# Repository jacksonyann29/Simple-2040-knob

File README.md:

# Simple-2040-knob
 PCB Design for a single rotary encoder HID, based on a RP2040 microcontroller.

## About
The goal of this project was to get more practice designing PCBs by implementing a microcontroller directly on a PCB. The current iteration successfully works except for USB programming and communication. USB power works, and programming over the SWD pins also works demonstrating that the RP2040 and flash were correctly configured including the crystal oscillator (at least for the simple led blink code tested on the device).

## Future Changes
*	Shorten the USB traces, use a surface mount usb port and double check impedance so USB communication will work.
*	Replace the crystal circuit with an external crystal oscillator IC which would hopefully be simpler to implement and more robust.
*	Add hardware debouncing to the encoder implementation.

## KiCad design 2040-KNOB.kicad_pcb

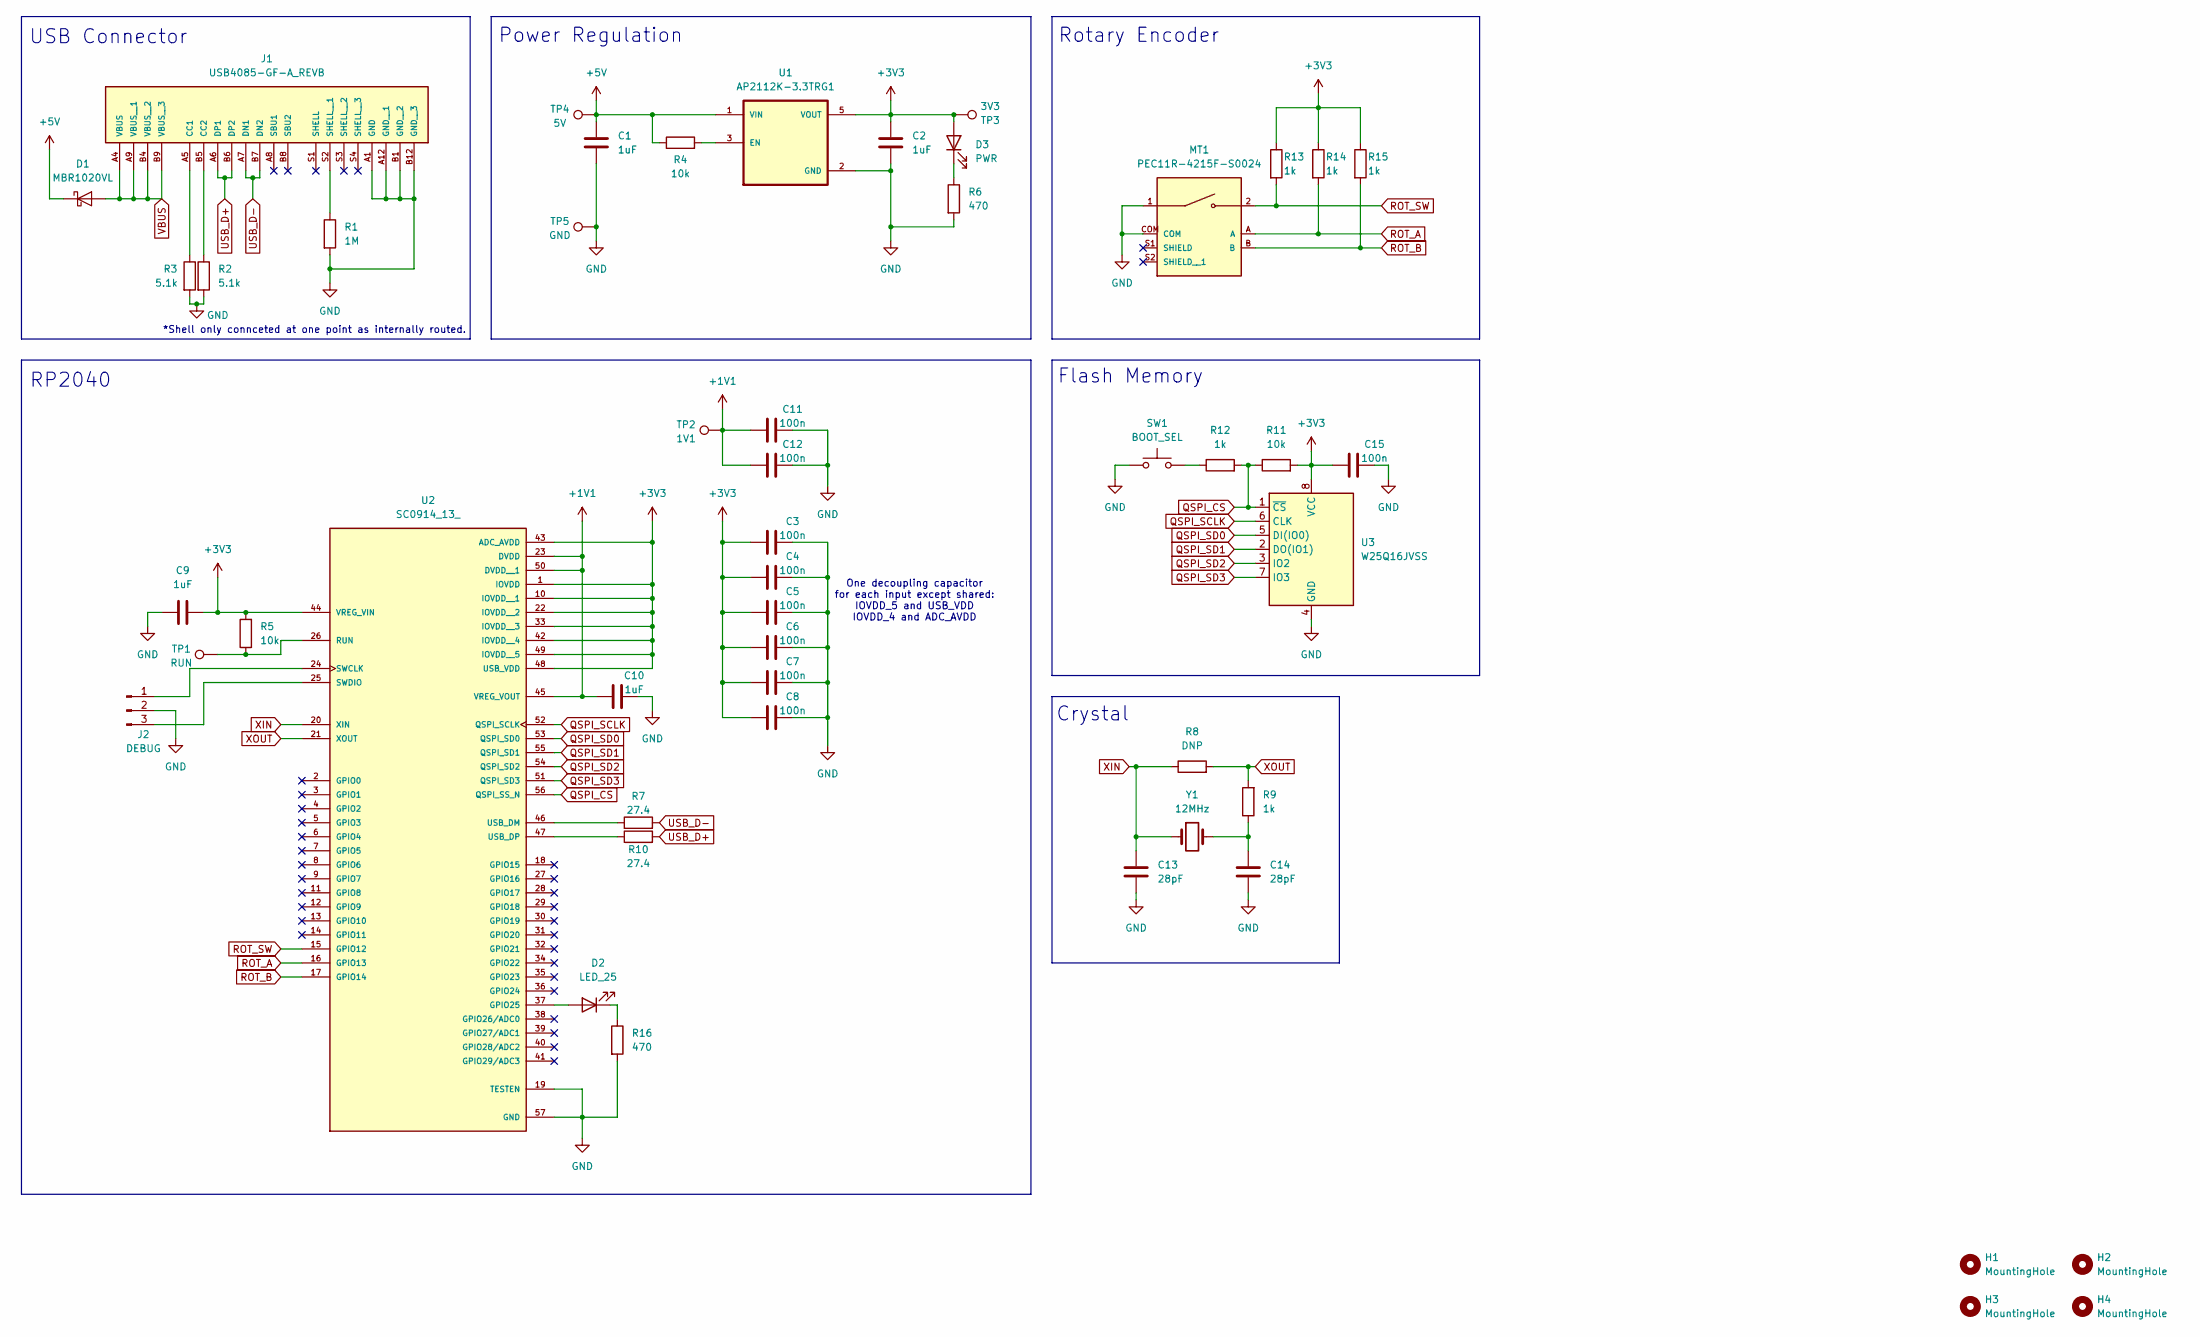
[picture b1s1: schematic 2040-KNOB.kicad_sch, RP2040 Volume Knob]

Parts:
C1, C2: 1uF; C_1206_3216Metric_Pad1.33x1.80mm_HandSolder
C3, C4, C5, C6, C7, C8, C11, C12, C15: 100n; C_0603_1608Metric_Pad1.08x0.95mm_HandSolder
C9, C10: 1uF; C_0805_2012Metric_Pad1.18x1.45mm_HandSolder
C13, C14: 28pF; C_0805_2012Metric_Pad1.18x1.45mm_HandSolder
D1: MBR1020VL; D_SOD-123F
D2: LED_25; LED_1206_3216Metric_Pad1.42x1.75mm_HandSolder
D3: PWR; LED_1206_3216Metric_Pad1.42x1.75mm_HandSolder
H1, H2, H3, H4: MountingHole; MountingHole_3.2mm_M3_ISO7380_Pad
J1: USB4085-GF-A_REVB; GCT_USB4085-GF-A_REVB; PARTREV B
J2: DEBUG; PinHeader_1x03_P2.54mm_Vertical
MT1: PEC11R-4215F-S0024; XDCR_PEC11R-4215F-S0024; PARTREV Rev. 09/19
R1: 1M; R_1206_3216Metric_Pad1.30x1.75mm_HandSolder
R2, R3: 5.1k; R_1206_3216Metric_Pad1.30x1.75mm_HandSolder
R4, R5, R11: 10k; R_1206_3216Metric_Pad1.30x1.75mm_HandSolder
R6, R16: 470; R_1206_3216Metric_Pad1.30x1.75mm_HandSolder
R7, R10: 27.4; R_0603_1608Metric_Pad0.98x0.95mm_HandSolder
R8: DNP; R_0603_1608Metric_Pad0.98x0.95mm_HandSolder
R9: 1k; R_0603_1608Metric_Pad0.98x0.95mm_HandSolder
R12, R13, R14, R15: 1k; R_1206_3216Metric_Pad1.30x1.75mm_HandSolder
SW1: BOOT_SEL; SW_PUSH_6mm
TP1: RUN; TestPoint_Pad_D1.5mm
TP2: 1V1; TestPoint_Pad_D1.5mm
TP3: 3V3; TestPoint_Pad_D1.5mm
TP4: 5V; TestPoint_Pad_D1.5mm
TP5: GND; TestPoint_Pad_D1.5mm
U1: AP2112K-3.3TRG1; SOT95P285X140-5N; PARTREV 2-2
U2: SC0914_13_; QFN40P700X700X90-57N; PARTREV 2.2
U3: W25Q16JVSS; SOIC-8_5.23x5.23mm_P1.27mm
Y1: 12MHz; XTAL_ABLS7M-12.000MHZ-B-2-T

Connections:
+1V1: C10.2, C11.1, C12.1, TP2.1, U2.23 (DVDD), U2.45 (VREG_VOUT), U2.50 (DVDD__1)
+3V3: C2.1, C3.1, C4.1, C5.1, C6.1, C7.1, C8.1, C9.2, C15.1, D3.2 (A), R5.2, R11.2, R13.1, R14.1, R15.1, TP3.1, U1.5 (VOUT), U2.1 (IOVDD), U2.10 (IOVDD__1), U2.22 (IOVDD__2), U2.33 (IOVDD__3), U2.42 (IOVDD__4), U2.43 (ADC_AVDD), U2.44 (VREG_VIN), U2.48 (USB_VDD), U2.49 (IOVDD__5), U3.8 (VCC)
+5V: C1.1, D1.1 (K), R4.1, TP4.1, U1.1 (VIN)
GND: C1.2, C2.2, C3.2, C4.2, C5.2, C6.2, C7.2, C8.2, C9.1, C10.1, C11.2, C12.2, C13.1, C14.1, C15.2, J1.A1 (GND), J1.A12 (GND__1), J1.B1 (GND__2), J1.B12 (GND__3), J2.2, MT1.1, MT1.COM, R1.2, R2.2, R3.2, R6.2, R16.2, SW1.1, TP5.1, U1.2 (GND), U2.19 (TESTEN), U2.57 (GND), U3.4 (GND)
unnamed: C14.2, R9.1, Y1.2
unnamed: D2.2 (A), U2.37 (GPIO25)
unnamed: D2.1 (K), R16.1
unnamed: D3.1 (K), R6.1
unnamed: J1.A5 (CC1), R3.1
unnamed: J1.B5 (CC2), R2.1
unnamed: J1.S2 (SHELL__1), R1.1
unnamed: J2.1, U2.24 (SWCLK)
unnamed: J2.3, U2.25 (SWDIO)
unnamed: R12.1, SW1.2
unnamed: R4.2, U1.3 (EN)
unnamed: R5.1, TP1.1, U2.26 (RUN)
unnamed: R7.1, U2.46 (USB_DM)
unnamed: R10.1, U2.47 (USB_DP)
QSPI_CS: R11.1, R12.2, U2.56 (QSPI_SS_N), U3.1 (~CS)
QSPI_SCLK: U2.52 (QSPI_SCLK), U3.6 (CLK)
QSPI_SD0: U2.53 (QSPI_SD0), U3.5 (DI(IO0))
QSPI_SD1: U2.55 (QSPI_SD1), U3.2 (DO(IO1))
QSPI_SD2: U2.54 (QSPI_SD2), U3.3 (IO2)
QSPI_SD3: U2.51 (QSPI_SD3), U3.7 (IO3)
ROT_A: MT1.A, R14.2, U2.16 (GPIO13)
ROT_B: MT1.B, R15.2, U2.17 (GPIO14)
ROT_SW: MT1.2, R13.2, U2.15 (GPIO12)
USB_D+: J1.A6 (DP1), J1.B6 (DP2), R10.2
USB_D-: J1.A7 (DN1), J1.B7 (DN2), R7.2
VBUS: D1.2 (A), J1.A4 (VBUS), J1.A9 (VBUS__1), J1.B4 (VBUS__2), J1.B9 (VBUS__3)
XIN: C13.2, R8.1, U2.20 (XIN), Y1.1
XOUT: R8.2, R9.2, U2.21 (XOUT)

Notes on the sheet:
One decoupling capacitor for each input except shared: IOVDD_5 and USB_VDD IOVDD_4 and ADC_AVDD
Rotary Encoder
RP2040
Power Regulation
Flash Memory
USB Connector
*Shell only connceted at one point as internally routed.
Crystal

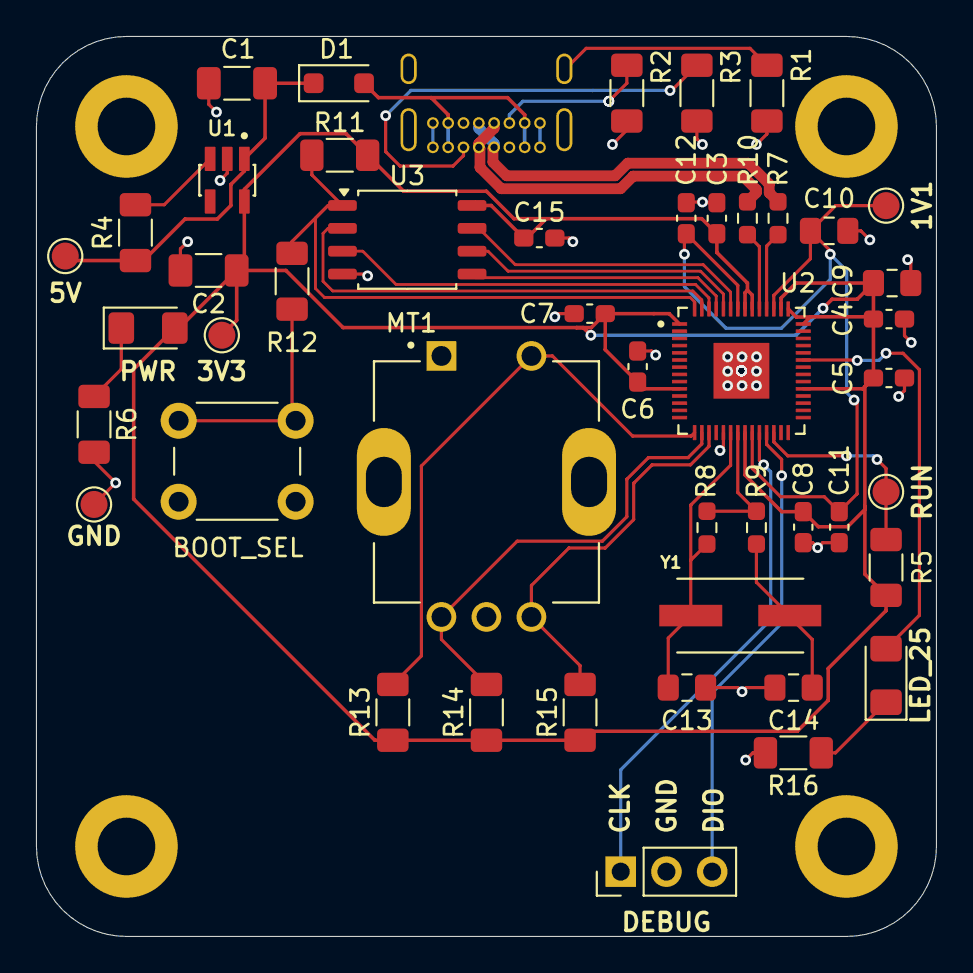
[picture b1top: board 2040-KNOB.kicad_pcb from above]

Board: 2 copper layers, 50.0 x 50.0 mm, 51 parts (1 on the bottom side), 32 nets.

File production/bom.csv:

Designator,Footprint,Quantity,Value,LCSC Part #
"C1, C2",1206,2,1uF,
"C10, C9",0805,2,1uF,
"C11, C12, C15, C3, C4, C5, C6, C7, C8",0603,9,100n,
C13,0805,1,29pF,
C14,0805,1,27pF,
D1,D_SOD-123F,1,MBR1020VL,
D2,1206,1,LED_25,
D3,1206,1,PWR,
J1,GCT_USB4085-GF-A_REVB,1,USB4085-GF-A_REVB,
J2,PinHeader_1x03_P2.54mm_Vertical,1,DEBUG,
MT1,XDCR_PEC11R-4215F-S0024,1,PEC11R-4215F-S0024,
R1,1206,1,1M,
"R10, R7",0603,2,27.4,
"R11, R4, R5",1206,3,10k,
"R12, R13, R14, R15",1206,4,1k,
"R16, R6",1206,2,470,
"R2, R3",1206,2,5.1k,
R8,0603,1,DNP,
R9,0603,1,1k,
SW1,SW_PUSH_6mm,1,BOOT_SEL,
TP1,TestPoint_Pad_D1.5mm,1,RUN,
TP2,TestPoint_Pad_D1.5mm,1,1V1,
TP3,TestPoint_Pad_D1.5mm,1,3V3,
TP4,TestPoint_Pad_D1.5mm,1,5V,
TP5,TestPoint_Pad_D1.5mm,1,GND,
U1,SOT95P285X140-5N,1,AP2112K-3.3TRG1,
U2,QFN40P700X700X90-57N,1,SC0914_13_,
U3,SOIC-8_5.23x5.23mm_P1.27mm,1,W25Q16JVSS,
Y1,XTAL_ABLS7M-12.000MHZ-B-2-T,1,12MHz,

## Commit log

2025-04-14 Included project files within repo
2025-06-09 Create Gitignore
2025-06-09 Remove backups
